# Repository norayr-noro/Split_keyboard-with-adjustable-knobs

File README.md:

# ⌨️ Split Keyboard Project
Making your own keyboard sounds difficult, but it really isn't! And this repo is proof of that. As a beginner in the field of CAD and PCB design, this is an ideal project to make because it combines areas like PCB and CAD modeling, and in this repo, I'll be writing on how I built it following the guide on hackclub stasis!

---
## Components
Here I'll put down all the components I will likely use in the full project:
|ITEM | URL | QUANTITY |PRICE (USD) |
|-------| ------| ---------------| ---------- |
|cherry-mx style switches| https://www.ebay.co.uk/itm/187479375359| 56 | 14.58|
|1N5819 diodes|https://www.rapidonline.com/st-1n5819-schottky-diode-40v-1a-do41-47-2566|56| 5.4| 
|Raspberry Pi Pico W|https://shorturl.at/rgenT|2|15.57|
|EC11E rotary encoders|https://www.adafruit.com/product/377|2|9|
|LiPo batteries (1500mah)	|https://shorturl.at/IHMxN|2|18.79|
|TP4056 modules|https://www.ebay.co.uk/itm/295410567795?var=593544577789|2|3.22|
|SS12D10 slide switches|	https://shorturl.at/kdSMI|2|2.68|

---
## Libraries
All libraries I used are in the Stasis Hackclub guide(https://stasis.hackclub.com/starter-projects/split-keyboard) + I also used the symbols and footprints for the Raspberry Pi from ScottoKeeb's (I recommend checking him out for anything custom keyboard related!!his YouTube channel is https://www.youtube.com/watch?v=8WXpGTIbxlQ&list=PLBD2IS_t_iWZDMdG_ZF57x9Ebm3kxKqxF&index=3)

## 🧠 Design 
Because I used the hackclbu split keyboard tutorial as a foundation, one of the biggest changes was switching from the XIAO nRF52840 (SMD) to the Raspberry Pi Pico. The reason for that is mostly for convenience, as I had a few picos lying around and also more GPIO pins to make a proper keyboard.(more pins = more rows/columbs = more keys), And with the diode+switch matrix would make an ideal build.

---

### 🔄 Rotary Encoders

I also added these rotary encoders(one in each hand) to control the sound and brightness of the screen. These just make the design more fun and unique, and it would not change a lot if these were not on the PCB, so feel free to change stuff around!

---

## UPDATES
 Changed the full design of the PCB to make it as slim as possible (could've done better tbh) to lower the cost of manufacturing the PCB + the fact it would look like a cleaner and nicer build in general. After that, I shifted the Pico W upwards (all the wayyyyyy to the edge) for easier access to the USB port and simpler routing and debugging
Continuing with those changes, I moved on to the CAD models, changed the case and plate to fit the new PCB, and mostly did some polishing for where the USB-C would go and where the slide switch should go. 

I also put the pico to the edge to easily debug and a lot of dat. Cant wait to build this!

## Photos of where I'm at now 

Herese the final full assembly of the case and plate (looks a bit chonky but still not bad): (THE NEW MODEL)

I'll also attach the .step file for the PCB and the .f3d file for the 3d model i  have worked on to this repository for future reference...

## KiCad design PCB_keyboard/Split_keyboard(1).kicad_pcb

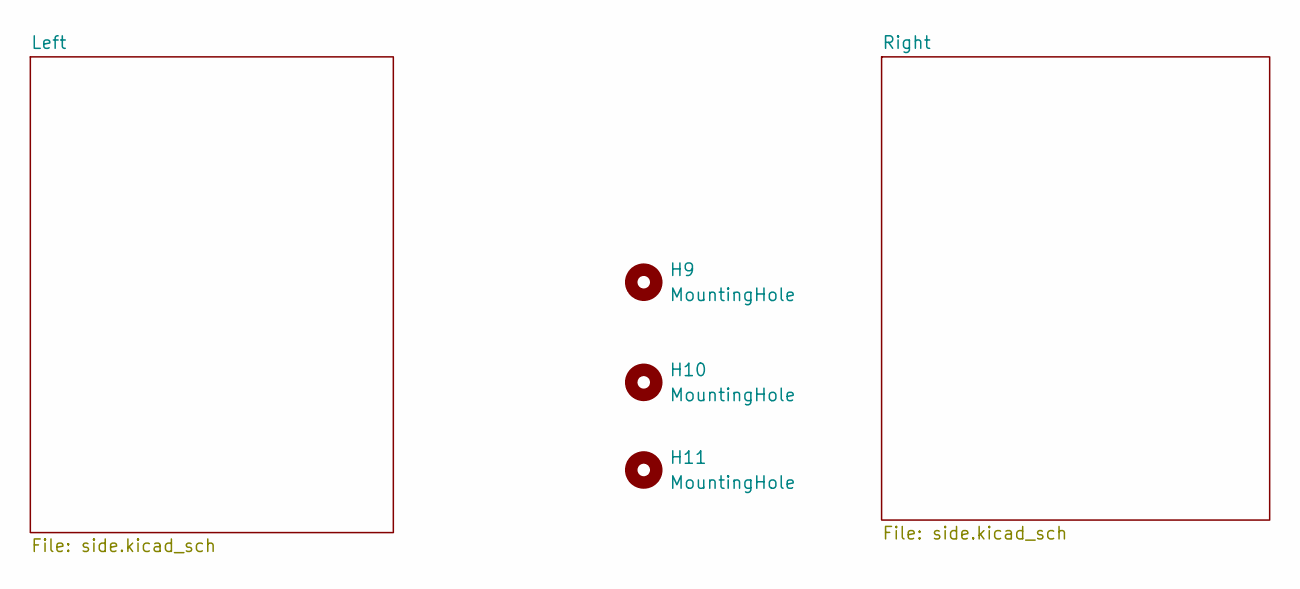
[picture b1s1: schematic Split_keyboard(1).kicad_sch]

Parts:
H9, H10, H11: MountingHole; mouse-bite-5mm-slot

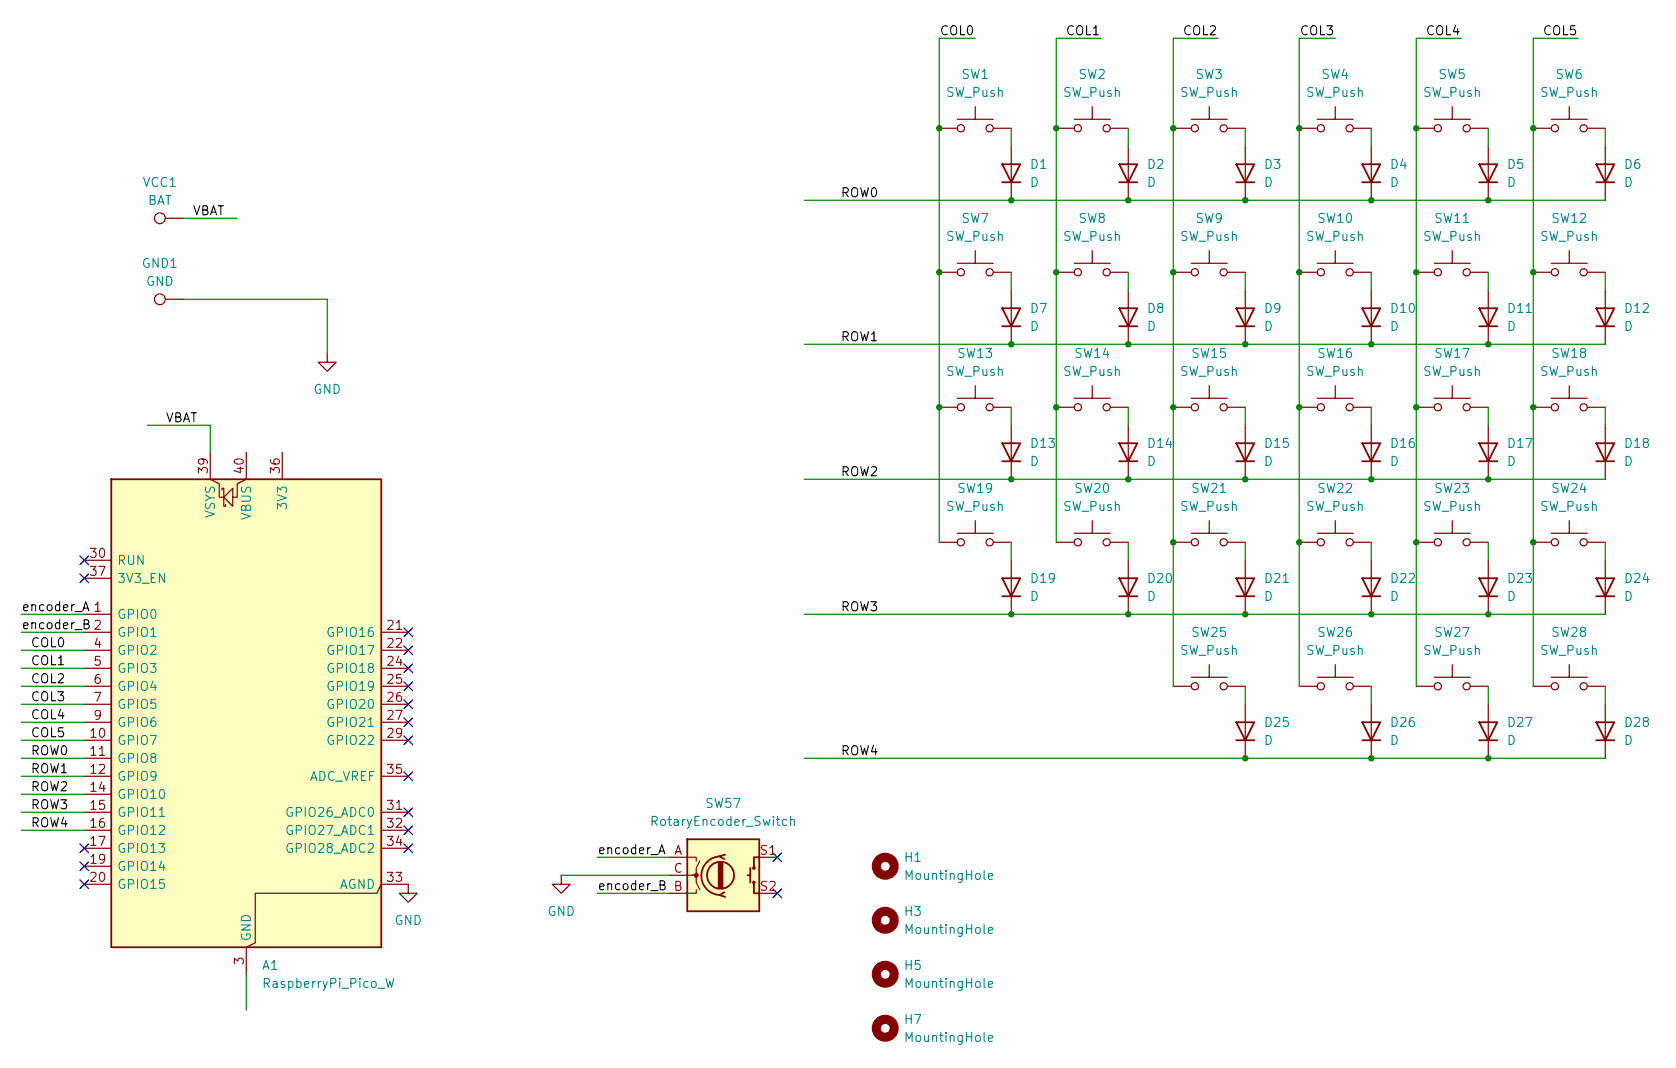
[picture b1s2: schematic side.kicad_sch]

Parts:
A1: RaspberryPi_Pico_W; RaspberryPi_Pico_Common_THT
D1, D2, D3, D4, D5, D6, D7, D8, D9, D10, D11, D12, D13, D14, D15, D16, D17, D18, D19, D20, D21, D22, D23, D24, D25, D26, D27, D28: D; D_DO-35_SOD27_P7.62mm_Horizontal
GND1: GND; TestPoint_Pad_D2.0mm
H1, H3, H5, H7: MountingHole; MountingHole_2.2mm_M2
SW1, SW2, SW3, SW4, SW5, SW6, SW7, SW8, SW9, SW10, SW11, SW12, SW13, SW14, SW15, SW16, SW17, SW18, SW19, SW20, SW21, SW22, SW23, SW24, SW25, SW26, SW27, SW28: SW_Push; SW_Cherry_MX_1.00u_PCB
SW57: RotaryEncoder_Switch; RotaryEncoder_Alps_EC11E-Switch_Vertical_H20mm
VCC1: BAT; TestPoint_Pad_D2.0mm

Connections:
/Left/COL0: A1.4 (GPIO2), SW1.1, SW7.1, SW13.1, SW19.1
/Left/COL1: A1.5 (GPIO3), SW2.1, SW8.1, SW14.1, SW20.1
/Left/COL2: A1.6 (GPIO4), SW3.1, SW9.1, SW15.1, SW21.1, SW25.1
/Left/COL3: A1.7 (GPIO5), SW4.1, SW10.1, SW16.1, SW22.1, SW26.1
/Left/COL4: A1.9 (GPIO6), SW5.1, SW11.1, SW17.1, SW23.1, SW27.1
/Left/COL5: A1.10 (GPIO7), SW6.1, SW12.1, SW18.1, SW24.1, SW28.1
/Left/ROW0: A1.11 (GPIO8), D1.1 (K), D2.1 (K), D3.1 (K), D4.1 (K), D5.1 (K), D6.1 (K)
/Left/ROW1: A1.12 (GPIO9), D7.1 (K), D8.1 (K), D9.1 (K), D10.1 (K), D11.1 (K), D12.1 (K)
/Left/ROW2: A1.14 (GPIO10), D13.1 (K), D14.1 (K), D15.1 (K), D16.1 (K), D17.1 (K), D18.1 (K)
/Left/ROW3: A1.15 (GPIO11), D19.1 (K), D20.1 (K), D21.1 (K), D22.1 (K), D23.1 (K), D24.1 (K)
/Left/ROW4: A1.16 (GPIO12), D25.1 (K), D26.1 (K), D27.1 (K), D28.1 (K)
/Left/VBAT: A1.39 (VSYS), VCC1.1 (1_1)
/Left/encoder_A: A1.1 (GPIO0), SW57.A
/Left/encoder_B: A1.2 (GPIO1), SW57.B
GND: A1.33 (AGND), GND1.1 (1_1), SW57.C; also elsewhere on the board
unnamed: A1.3 (GND), A1.8 (GND), A1.13 (GND), A1.18 (GND), A1.23 (GND), A1.28 (GND), A1.38 (GND)
unnamed: D1.2 (A), SW1.2
unnamed: D2.2 (A), SW2.2
unnamed: D3.2 (A), SW3.2
unnamed: D4.2 (A), SW4.2
unnamed: D5.2 (A), SW5.2
unnamed: D6.2 (A), SW6.2
unnamed: D7.2 (A), SW7.2
unnamed: D8.2 (A), SW8.2
unnamed: D9.2 (A), SW9.2
unnamed: D10.2 (A), SW10.2
unnamed: D11.2 (A), SW11.2
unnamed: D12.2 (A), SW12.2
unnamed: D13.2 (A), SW13.2
unnamed: D14.2 (A), SW14.2
unnamed: D15.2 (A), SW15.2
unnamed: D16.2 (A), SW16.2
unnamed: D17.2 (A), SW17.2
unnamed: D18.2 (A), SW18.2
unnamed: D19.2 (A), SW19.2
unnamed: D20.2 (A), SW20.2
unnamed: D21.2 (A), SW21.2
unnamed: D22.2 (A), SW22.2
unnamed: D23.2 (A), SW23.2
unnamed: D24.2 (A), SW24.2
unnamed: D25.2 (A), SW25.2
unnamed: D26.2 (A), SW26.2
unnamed: D27.2 (A), SW27.2
unnamed: D28.2 (A), SW28.2

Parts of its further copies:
A2: RaspberryPi_Pico_W; RaspberryPi_Pico_Common_THT
D29, D30, D31, D32, D33, D34, D35, D36, D37, D38, D39, D40, D41, D42, D43, D44, D45, D46, D47, D48, D49, D50, D51, D52, D53, D54, D55, D56: D; D_DO-35_SOD27_P7.62mm_Horizontal
GND2: GND; TestPoint_Pad_D2.0mm
H4, H6, H8: MountingHole; MountingHole_2.2mm_M2
SW29, SW30, SW31, SW32, SW33, SW34, SW35, SW36, SW37, SW38, SW39, SW40, SW41, SW42, SW43, SW44, SW45, SW46, SW47, SW48, SW49, SW50, SW51, SW52, SW53, SW54, SW55, SW56: SW_Push; SW_Cherry_MX_1.00u_PCB
SW58: RotaryEncoder_Switch; RotaryEncoder_Alps_EC11E-Switch_Vertical_H20mm
VCC2: BAT; TestPoint_Pad_D2.0mm

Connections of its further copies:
/Right/COL0: A2.4 (GPIO2), SW29.1, SW35.1, SW41.1, SW47.1
/Right/COL1: A2.5 (GPIO3), SW30.1, SW36.1, SW42.1, SW48.1
/Right/COL2: A2.6 (GPIO4), SW31.1, SW37.1, SW43.1, SW49.1, SW53.1
/Right/COL3: A2.7 (GPIO5), SW32.1, SW38.1, SW44.1, SW50.1, SW54.1
/Right/COL4: A2.9 (GPIO6), SW33.1, SW39.1, SW45.1, SW51.1, SW55.1
/Right/COL5: A2.10 (GPIO7), SW34.1, SW40.1, SW46.1, SW52.1, SW56.1
/Right/ROW0: A2.11 (GPIO8), D29.1 (K), D30.1 (K), D31.1 (K), D32.1 (K), D33.1 (K), D34.1 (K)
/Right/ROW1: A2.12 (GPIO9), D35.1 (K), D36.1 (K), D37.1 (K), D38.1 (K), D39.1 (K), D40.1 (K)
/Right/ROW2: A2.14 (GPIO10), D41.1 (K), D42.1 (K), D43.1 (K), D44.1 (K), D45.1 (K), D46.1 (K)
/Right/ROW3: A2.15 (GPIO11), D47.1 (K), D48.1 (K), D49.1 (K), D50.1 (K), D51.1 (K), D52.1 (K)
/Right/ROW4: A2.16 (GPIO12), D53.1 (K), D54.1 (K), D55.1 (K), D56.1 (K)
/Right/VBAT: A2.39 (VSYS), VCC2.1 (1_1)
/Right/encoder_A: A2.1 (GPIO0), SW58.A
/Right/encoder_B: A2.2 (GPIO1), SW58.B
GND: A2.33 (AGND), GND2.1 (1_1), SW58.C; also elsewhere on the board
unnamed: A2.3 (GND), A2.8 (GND), A2.13 (GND), A2.18 (GND), A2.23 (GND), A2.28 (GND), A2.38 (GND)
unnamed: D29.2 (A), SW29.2
unnamed: D30.2 (A), SW30.2
unnamed: D31.2 (A), SW31.2
unnamed: D32.2 (A), SW32.2
unnamed: D33.2 (A), SW33.2
unnamed: D34.2 (A), SW34.2
unnamed: D35.2 (A), SW35.2
unnamed: D36.2 (A), SW36.2
unnamed: D37.2 (A), SW37.2
unnamed: D38.2 (A), SW38.2
unnamed: D39.2 (A), SW39.2
unnamed: D40.2 (A), SW40.2
unnamed: D41.2 (A), SW41.2
unnamed: D42.2 (A), SW42.2
unnamed: D43.2 (A), SW43.2
unnamed: D44.2 (A), SW44.2
unnamed: D45.2 (A), SW45.2
unnamed: D46.2 (A), SW46.2
unnamed: D47.2 (A), SW47.2
unnamed: D48.2 (A), SW48.2
unnamed: D49.2 (A), SW49.2
unnamed: D50.2 (A), SW50.2
unnamed: D51.2 (A), SW51.2
unnamed: D52.2 (A), SW52.2
unnamed: D53.2 (A), SW53.2
unnamed: D54.2 (A), SW54.2
unnamed: D55.2 (A), SW55.2
unnamed: D56.2 (A), SW56.2

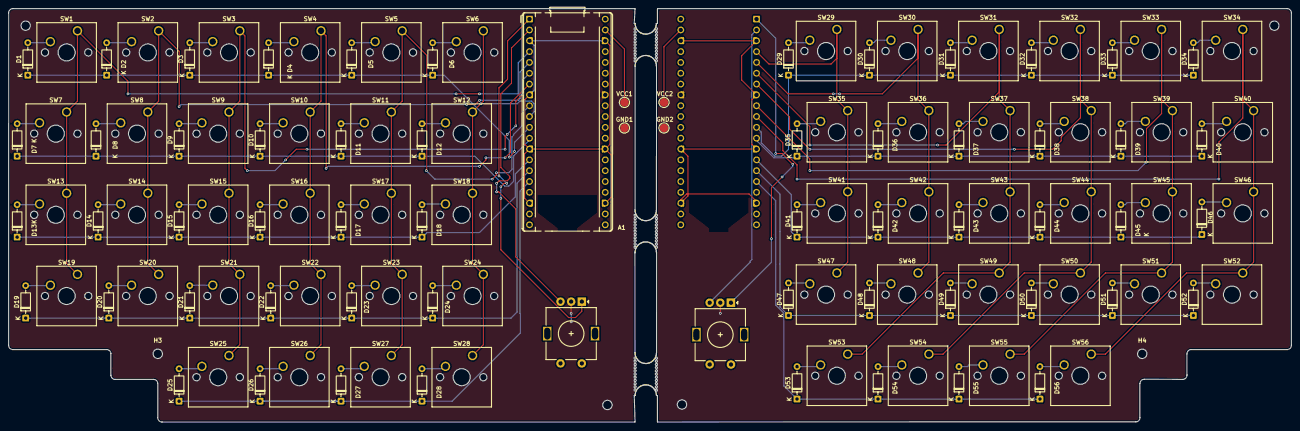
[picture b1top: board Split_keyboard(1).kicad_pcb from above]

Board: 2 copper layers, 301.0 x 97.0 mm, 129 parts (1 on the bottom side), 87 nets.

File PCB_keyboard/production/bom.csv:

Designator,Footprint,Quantity,Value,LCSC Part #
"A1, A2",RaspberryPi_Pico_Common_THT,2,RaspberryPi_Pico_W,
"D1, D10, D11, D12, D13, D14, D15, D16, D17, D18, D19, D2, D20, D21, D22, D23, D24, D25, D26, D27, D28, D29, D3, D30, D31, D32, D33, D34, D35, D36, D37, D38, D39, D4, D40, D41, D42, D43, D44, D45, D46, D47, D48, D49, D5, D50, D51, D52, D53, D54, D55, D56, D6, D7, D8, D9",D_DO-35_SOD27_P7.62mm_Horizontal,56,D,
"GND1, GND2",TestPoint_Pad_D2.0mm,2,GND,
"SW1, SW10, SW11, SW12, SW13, SW14, SW15, SW16, SW17, SW18, SW19, SW2, SW20, SW21, SW22, SW23, SW24, SW25, SW26, SW27, SW28, SW29, SW3, SW30, SW31, SW32, SW33, SW34, SW35, SW36, SW37, SW38, SW39, SW4, SW40, SW41, SW42, SW43, SW44, SW45, SW46, SW47, SW48, SW49, SW5, SW50, SW51, SW52, SW53, SW54, SW55, SW56, SW6, SW7, SW8, SW9",SW_Cherry_MX_1.00u_PCB,56,SW_Push,
"SW57, SW58",RotaryEncoder_Alps_EC11E-Switch_Vertical_H20mm,2,RotaryEncoder_Switch,
"VCC1, VCC2",TestPoint_Pad_D2.0mm,2,BAT,

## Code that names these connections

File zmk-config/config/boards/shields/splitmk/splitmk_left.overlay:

/*
 * SplitMK Left Hand
 * god please eviserate the person who made C
 * (28 active keys + 2 TRNS)
 * Encoder: A=GP0  B=GP1  no SW :sad:
 * 
 * Diode orientation: COL2ROW obvously
 */

/ {
    chosen {
        zmk,kscan    = &kscan0;
        zmk,matrix_transform = &matrix_transform;
    };

    /* ── Key matrix  */
    kscan0: kscan {
        compatible = "zmk,kscan-gpio-matrix";
        label = "KSCAN";
        diode-direction = "col2row";

        row-gpios
            = <&gpio0  8 (GPIO_ACTIVE_HIGH | GPIO_PULL_DOWN)>   /* ROW0 GP8  */
            , <&gpio0  9 (GPIO_ACTIVE_HIGH | GPIO_PULL_DOWN)>   /* ROW1 GP9  */
            , <&gpio0  10 (GPIO_ACTIVE_HIGH | GPIO_PULL_DOWN)>   /* ROW2 GP10  */
            , <&gpio0  11 (GPIO_ACTIVE_HIGH | GPIO_PULL_DOWN)>   /* ROW3 GP11  */
            , <&gpio0  12 (GPIO_ACTIVE_HIGH | GPIO_PULL_DOWN)>   /* ROW4 GP12  */
            ;

        col-gpios
            = <&gpio0  2 GPIO_ACTIVE_HIGH>   /* COL0 GP2  */
            , <&gpio0  3 GPIO_ACTIVE_HIGH>   /* COL1 GP3  */
            , <&gpio0  4 GPIO_ACTIVE_HIGH>   /* COL2 GP4  */
            , <&gpio0  5 GPIO_ACTIVE_HIGH>   /* COL3 GP5  */
            , <&gpio0  6 GPIO_ACTIVE_HIGH>   /* COL4 GP6 */
            , <&gpio0  7 GPIO_ACTIVE_HIGH>   /* COL5 GP7 */
            ;
    };

    /* ── Matrix transform */
    matrix_transform: keymap_transform_0 {
        compatible = "zmk,matrix-transform";
        columns = <6>;
        rows = <5>;
        /*
         * map of actuall positions
         * Row 4 cols 4-5 are unused (TRNS) on your 28-key design
         */
        map = <
            RC(0,0) RC(0,1) RC(0,2) RC(0,3) RC(0,4) RC(0,5)
            RC(1,0) RC(1,1) RC(1,2) RC(1,3) RC(1,4) RC(1,5)
            RC(2,0) RC(2,1) RC(2,2) RC(2,3) RC(2,4) RC(2,5)
            RC(3,0) RC(3,1) RC(3,2) RC(3,3) RC(3,4) RC(3,5)
            RC(4,0) RC(4,1) RC(4,2) RC(4,3) RC(4,4) RC(4,5)
        >;
    };

    /* ── Rotary encoder  */
    encoder_left: encoder_left {
        compatible = "alps,ec11";
        label = "LEFT_ENCODER";
        a-gpios = <&gpio0 0 (GPIO_ACTIVE_HIGH | GPIO_PULL_UP)>;
        b-gpios = <&gpio0 1 (GPIO_ACTIVE_HIGH | GPIO_PULL_UP)>;
        steps = <80>;                 /* 20 detents × 4 = 80 steps */
        status = "okay";
    };

    sensors {
        compatible = "zmk,keymap-sensors";
        sensors = <&encoder_left>;
        triggers-per-rotation = <20>;
    };
};

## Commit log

2026-04-26 Revise README with comprehensive project details
    Expanded the README to provide detailed project information, including components, design choices, firmware, current progress, goals, features, next steps, and final thoughts.
2026-04-26 Create photos
2026-04-26 Create PCB
2026-04-26 Create 3D model case+plate
2026-04-26 Add Libraries section to README
    Added a section for libraries used in the project with references.
2026-04-26 Update README with project photos and file attachments
    Added photos and additional files for reference.
2026-04-26 Revise design choices and goals sections in README
    Updated sections in README.md for clarity and organization.
2026-05-01 Fix typos and enhance README content
    Corrected typos and improved clarity in the README.
2026-05-01 Update README with clearer project overview
    Revised project description for clarity and focus on beginner accessibility.
2026-05-01 Complete rework of README
    Updated README to clarify project components, design process, and current progress. Improved grammar and consistency throughout the document.
2026-05-02 Update README with component sources and details
    Added sources and additional details for components used in the split keyboard project. (forgot heh...)
2026-05-03 Add files via upload
    Added the full STLs separately for 3d printing! changed and updated the case for a more low profile build
2026-05-03 Add files via upload
    Sorry for interupting the review had to recheck the pcb for errors because i changed the diodes from smd to tht because i had the tht diodes already(Sorryyyy)
2026-05-08 Revise README with project updates and final thoughts
    Updated the README to reflect changes in the PCB design, CAD models, and added a BOM file. Included final thoughts on the project experience.
2026-05-08 Revise README with updates on PCB and BOM
    Updated the README to reflect changes in PCB design, CAD models, and added a BOM file for parts sourcing.
2026-05-08 Update README with detailed note to reviewer
    Clarified note to reviewer regarding BOM and project funding.
2026-06-04 Delete PCB_keyboard directory
    new pcb on the way!
2026-06-04 Delete 3D model case+plate directory
    CAD model on the wayyyy
2026-06-04 Revise README for clarity and updates
    Corrected typos and improved clarity in the README. Updated component list and added links for sourcing parts. Enhanced project description and final thoughts.
2026-06-04 Update README with new image and project details
    Added an image of the keyboard project and updated the introduction.
2026-06-04 Update URLs and maintain BOM structure
    Updated URLs for Raspberry Pi Pico W, LiPo batteries, and SS12D10 slide switches to shortened links.
2026-06-04 Update README with components table
    Added a table listing components with URLs, quantities, and prices.
2026-06-11 Revise README for clarity and corrections
    Updated the README to improve clarity and fix typos.
2026-06-11 Fix typos and enhance README content
    Corrected typos and improved clarity in project description and design sections.
2026-06-11 Improve README.md clarity and details
    Updated descriptions for rotary encoders and PCB design changes. + added desciption and clarification for pushing the pico to the edge
2026-06-11 Delete PCB_keyboard directory
    final pcb on the way!
2026-06-11 Add files via upload
    final PCB (I hope)
2026-06-11 Update images in README.md
    Removed old images and added new images to the README.
2026-06-11 Fix typos and enhance readability in README.md
    Corrected typos and improved clarity in README.
2026-06-11 Update README to improve project description
    Revised introduction to clarify project scope and ease of learning.
2026-06-11 Replace old image with new screenshot
    Updated image in README and added a new image. (meme image)
2026-06-11 Revise PCB design details and project updates
    Updated README with design changes and progress notes.
2026-06-16 Update README with final assembly image and fix typo
    Added an image of the final assembly and corrected a typo.
2026-06-16 Update README with final assembly images and files
    Add additional images and mention attached files for reference.
2026-06-16 Add files via upload
    assembly file as proof
2026-06-18 Add files via upload
    updated keeb
2026-06-18 Add files via upload
    yes its chonkier yes its less detailed but it works so who cares
2026-06-18 Revise final assembly section with new images
    Updated images and added new model description in README.
